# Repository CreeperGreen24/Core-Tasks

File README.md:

# Core-Tasks
I have compiled the tasks from week-2 to week-4 into this one repository,there are readme files in each week's directory along with all the neccessary documents required to be submitted.

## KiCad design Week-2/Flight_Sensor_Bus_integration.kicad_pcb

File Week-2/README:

https://docs.google.com/document/d/1RP_673V6_qW0KfhE1dqelf96GbfFQ1NsgKyUuUupC-k/edit?usp=sharing

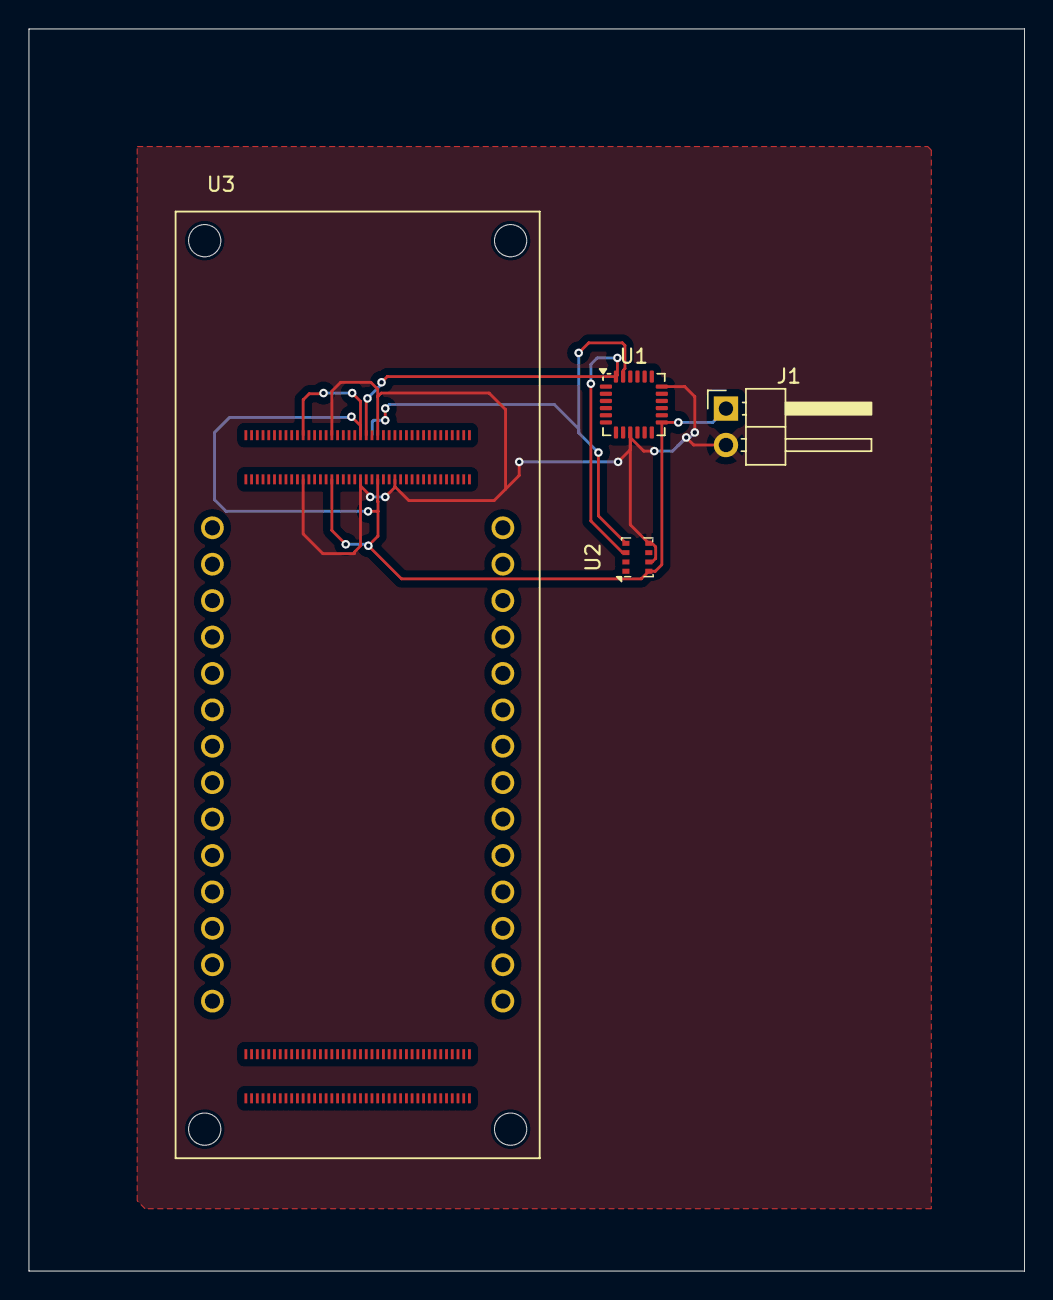
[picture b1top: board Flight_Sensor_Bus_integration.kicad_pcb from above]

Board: 4 copper layers, 69.5 x 86.7 mm, 4 parts (0 on the bottom side), 3 nets.

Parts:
J1: Conn_01x02_Pin; PinHeader_1x02_P2.54mm_Horizontal
U1: MPU-6050; InvenSense_QFN-24_4x4mm_P0.5mm
U2: BMP280; Bosch_LGA-8_2x2.5mm_P0.65mm_ClockwisePinNumbering
U3: ABX00042; MODULE_ABX00042

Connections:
+3.3V: J1.1, U1.13 (VDD), U2.8 (VDD), U3.J1_21 (VIN), U3.J1_32 (VIN), U3.J1_41 (VIN), U3.J1_48 (VIN)
/SDA: U1.24 (SDA), U2.3 (SDI), U3.J1_43 (I2C1_SDA)
GND: J1.2, U1.9 (AD0), U1.18 (GND), U2.5 (SDO), U2.7 (GND), U3.J1_22 (GND), U3.J1_31 (GND), U3.J1_42 (GND), U3.J1_47 (GND), U3.J1_54 (GND)

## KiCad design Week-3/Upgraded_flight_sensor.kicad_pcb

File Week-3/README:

https://docs.google.com/document/d/1ynIKvgqI1nZrBQeghkS2gB9ksT2LaIsWZPl-TCqRZSc/edit?usp=sharing

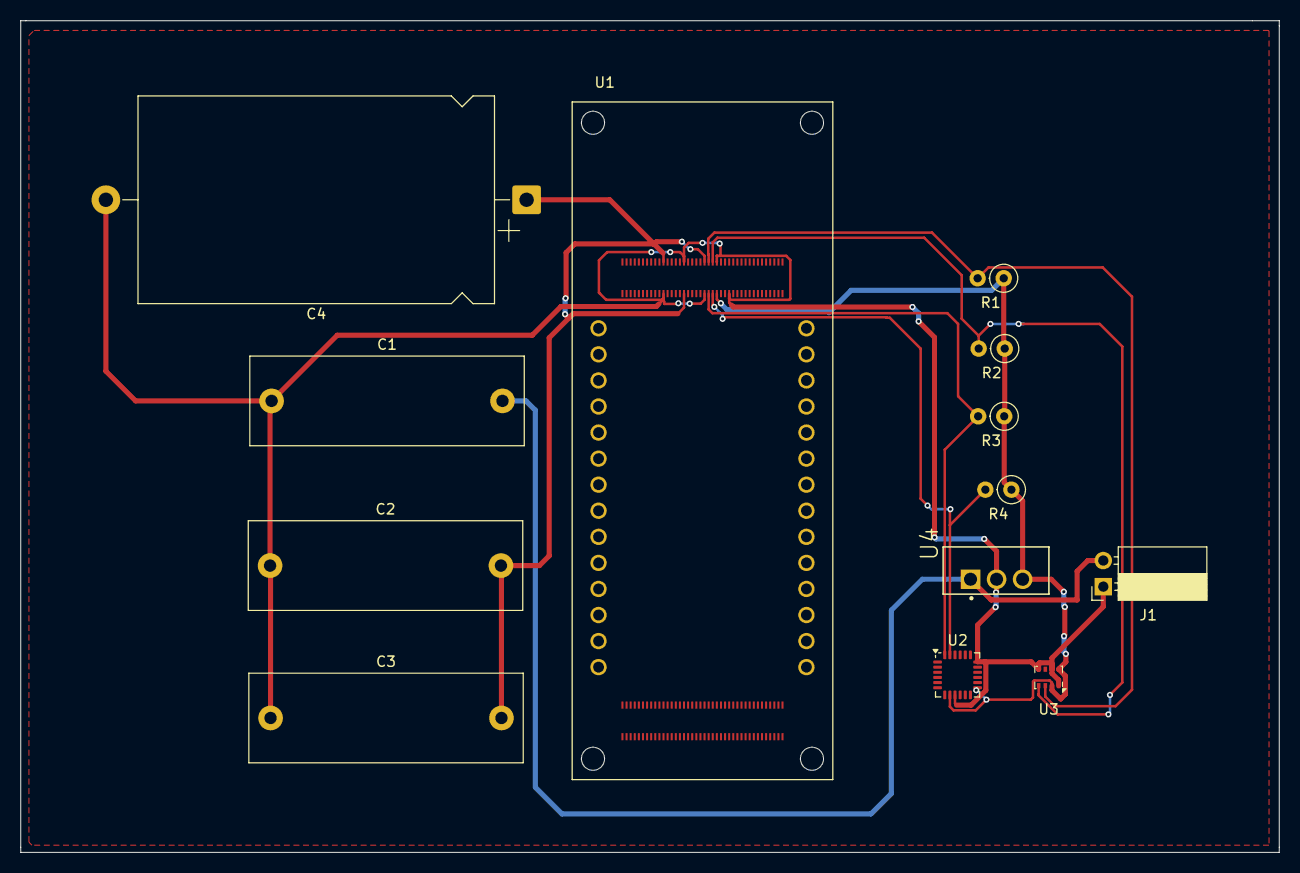
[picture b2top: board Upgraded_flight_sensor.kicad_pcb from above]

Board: 4 copper layers, 122.6 x 81.0 mm, 13 parts (0 on the bottom side), 7 nets.

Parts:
C1: 0.33uF; C_Rect_L26.5mm_W8.5mm_P22.50mm_MKS4
C2, C3: 0.1uF; C_Rect_L26.5mm_W8.5mm_P22.50mm_MKS4
C4: 10uF; CP_Axial_L34.5mm_D20.0mm_P41.00mm_Horizontal
J1: Conn_01x02_Socket; PinSocket_1x02_P2.54mm_Horizontal
R1, R2, R3, R4: 4.7k; R_Axial_DIN0207_L6.3mm_D2.5mm_P2.54mm_Vertical
U1: ABX00042; MODULE_ABX00042
U2: MPU-6050; InvenSense_QFN-24_4x4mm_P0.5mm
U3: BMP280; Bosch_LGA-8_2x2.5mm_P0.65mm_ClockwisePinNumbering
U4: L7805; TO254P460X1020X1945-3P

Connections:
+9V: C1.2, J1.2, U4.1 (IN)
/5V: C2.2, C3.2, C4.1, R1.1, R2.1, R3.1, R4.1, U1.J1_21 (VIN), U1.J1_32 (VIN), U1.J1_41 (VIN), U1.J1_48 (VIN), U2.8 (VLOGIC), U2.13 (VDD), U3.2 (CSB), U3.8 (VDD), U4.3 (OUT)
GND: C1.1, C2.1, C3.1, C4.2, J1.1, U1.J1_22 (GND), U1.J1_31 (GND), U1.J1_42 (GND), U1.J1_47 (GND), U1.J1_54 (GND), U2.9 (AD0), U2.18 (GND), U3.1 (GND), U3.5 (SDO), U3.7 (GND), U4.2 (GND)
unnamed: R4.2, U1.J1_46 (I2C0_SCL), U2.23 (SCL)
unnamed: R3.2, U1.J1_44 (I2C0_SDA), U2.24 (SDA)
unnamed: R2.2, U1.J1_45 (I2C1_SCL), U3.4 (SCK)
unnamed: R1.2, U1.J1_43 (I2C1_SDA), U3.3 (SDI)
